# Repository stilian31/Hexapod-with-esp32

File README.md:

# Hexapod-with-esp32
this is a custom control board for a six-legged (hexapod) robot. It’s built around the ESP32-S3 WROOM and uses two PCA9685 drivers to precisely control all servos. The robot can be easily controlled via a joystick, making movement intuitive and fun. Designed for DIY robotics projects and expandable with sensors or LEDs.
The 3D model of the hexapod IS NOT mine.I've adapted the 3D model for my PCB :)
If you have any questions you can text me on instagram @funtronics_ or @stilianskordas and on my gmail - stilianskordas08@gmail.com :). I will answer any time.

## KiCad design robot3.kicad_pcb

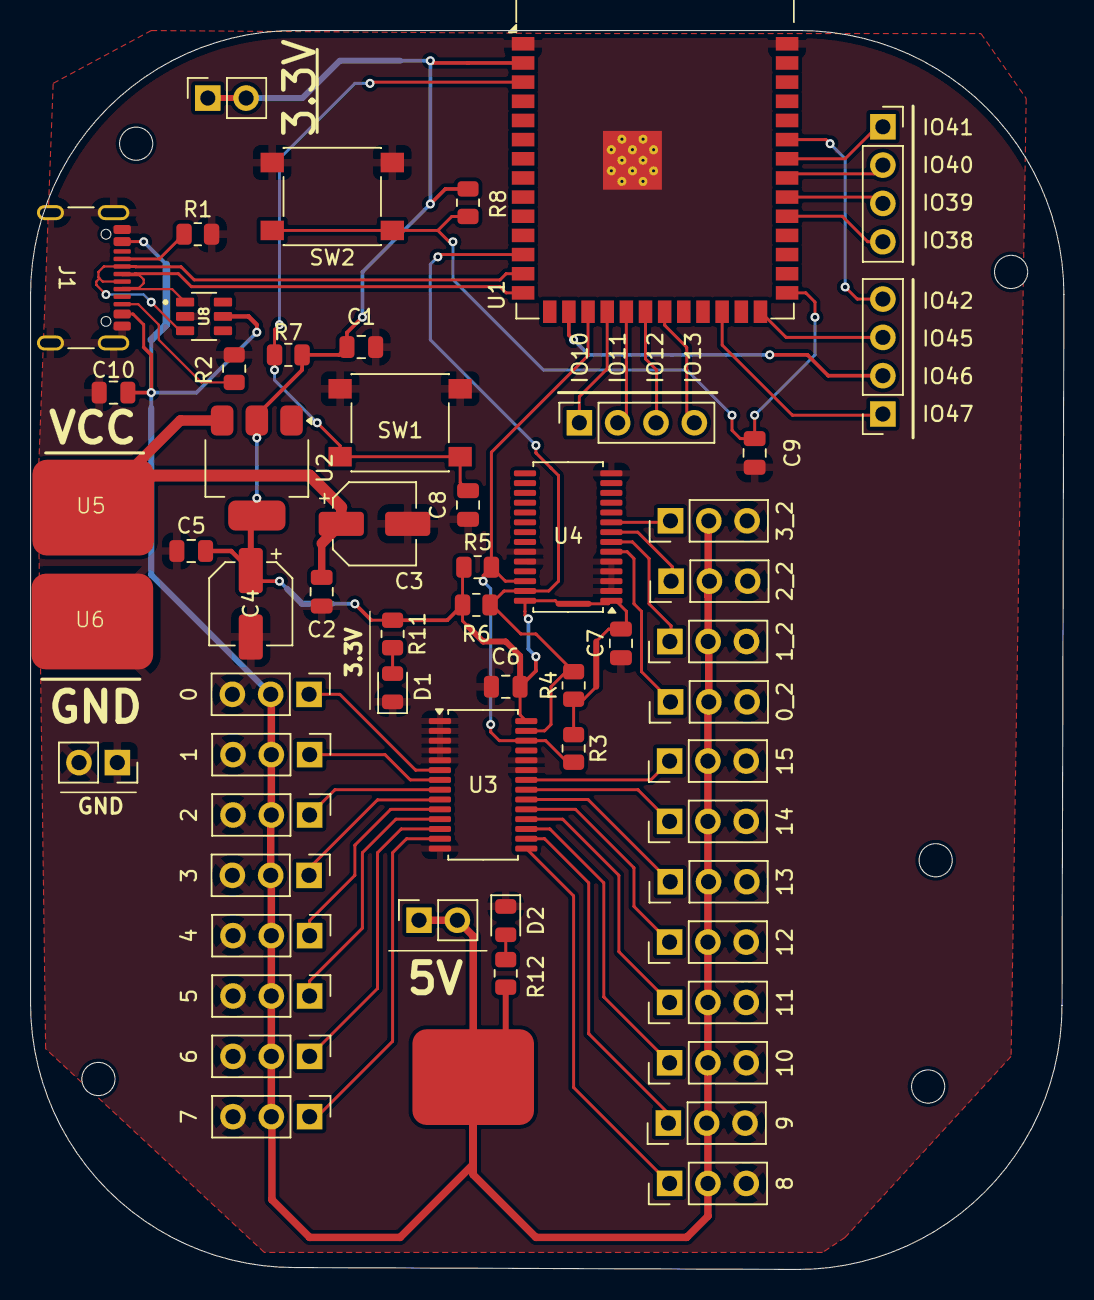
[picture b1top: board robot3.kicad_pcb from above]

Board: 2 copper layers, 68.5 x 82.1 mm, 59 parts (0 on the bottom side), 46 nets.

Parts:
0, 0_2, 1, 2, 2_2, 3, 4, 5, 6, 7, 8, 9, 10, 11, 12, 13, 14, 15: Conn_01x03_Pin; PinHeader_1x03_P2.54mm_Vertical
C1, C2, C5, C6, C7, C8, C9, C10: 100nF; C_0805_2012Metric
C3, C4: 10uF; CP_Elec_5x5.4
D1, D2: LED; LED_0805_2012Metric
J1: USB_C_Receptacle_USB2.0_16P; USB_C_Receptacle_GCT_USB4105-xx-A_16P_TopMnt_Horizontal
J19, J21: Conn_01x03_Pin; PinHeader_1x03_P2.54mm_Vertical
J22, J23, J24: Conn_01x04_Pin; PinSocket_1x04_P2.54mm_Vertical
J26, J27, J28: Conn_01x02_Pin; PinSocket_1x02_P2.54mm_Vertical
R1, R2: 5.1k; R_0805_2012Metric
R3, R5, R11, R12: R; R_0805_2012Metric
R4, R6: 4.7k; R_0805_2012Metric
R7, R8: 10k; R_0805_2012Metric
SW1, SW2: SW_Push; SW_SPST_PTS645
U1: ESP32-S3-WROOM-1
U2: AMS1117-3.3; SOT-223-3_TabPin2
U3, U4: PCA9685PW; TSSOP-28_4.4x9.7mm_P0.65mm
U5, U6, U7: pad
U8: USBLC6-2SC6

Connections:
+3.3V: C1.2, C4.1, C5.2, C6.2, C7.2, J27.1, J27.2, R3.1, R4.1, R5.1, R6.1, R7.1, R8.1, R11.1, U1.2 (3V3), U2.2 (VO), U3.28 (VDD), U4.1 (A0), U4.28 (VDD)
+5V: 0.2, 0_2.2, 1.2, 2.2, 2_2.2, 3.2, 4.2, 5.2, 6.2, 7.2, 8.2, 9.2, 10.2, 11.2, 12.2, 13.2, 14.2, 15.2, C10.1, J1.A4 (VBUS), J1.A9 (VBUS), J1.B4 (VBUS), J1.B9 (VBUS), J19.2, J21.2, J28.1, J28.2, R12.1, U7.1, U8.5
D+: J1.A6 (D+), J1.B6 (D+), U1.14 (USB_D+), U8.1
D-: J1.A7 (D-), J1.B7 (D-), U1.13 (USB_D-), U8.3
GND: 0.3, 0_2.3, 1.3, 2.3, 2_2.3, 3.3, 4.3, 5.3, 6.3, 7.3, 8.3, 9.3, 10.3, 11.3, 12.3, 13.3, 14.3, 15.3, C1.1, C2.1, C3.2, C4.2, C5.1, C6.1, C7.1, C8.2, C9.2, C10.2, D1.1 (K), D2.1 (K), J1.A1 (GND), J1.A12 (GND), J1.B1 (GND), J1.B12 (GND), J1.S1 (SHIELD), J19.3, J21.3, J26.1, J26.2, R1.2, R2.2, SW1.2, SW2.2, U1.1 (GND), U1.40 (GND), U1.41 (GND), U3.1 (A0), U3.2 (A1), U3.3 (A2), U3.4 (A3), U3.5 (A4), U3.14 (VSS), U3.23 (~OE), U3.24 (A5), U4.2 (A1), U4.3 (A2), U4.4 (A3), U4.5 (A4), U4.14 (VSS), U4.23 (~OE), U4.24 (A5), U6.1, U8.2
IO0: C9.1, R8.2, SW2.1, U1.27 (IO0)
IO8 SDA: R4.2, R6.2, U1.12 (IO8), U3.27 (SDA), U4.27 (SDA)
IO9 SCL: R3.2, R5.2, U1.17 (IO9), U3.26 (SCL), U4.26 (SCL)
LED0: 0.1, U3.6 (LED0)
LED0_2: 0_2.1, U4.6 (LED0)
LED1: 1.1, U3.7 (LED1)
LED1_2: J19.1, U4.7 (LED1)
LED2: 2.1, U3.8 (LED2)
LED2_2: 2_2.1, U4.8 (LED2)
LED3: 3.1, U3.9 (LED3)
LED3_2: J21.1, U4.9 (LED3)
LED4: 4.1, U3.10 (LED4)
LED5: 5.1, U3.11 (LED5)
LED6: 6.1, U3.12 (LED6)
LED7: 7.1, U3.13 (LED7)
LED8: 8.1, U3.15 (LED8)
LED9: 9.1, U3.16 (LED9)
LED10: 10.1, U3.17 (LED10)
LED11: 11.1, U3.18 (LED11)
LED12: 12.1, U3.19 (LED12)
LED13: 13.1, U3.20 (LED13)
LED14: 14.1, U3.21 (LED14)
LED15: 15.1, U3.22 (LED15)
unnamed: D1.2 (A), R11.2
unnamed: D2.2 (A), R12.2
unnamed: J1.A5 (CC1), R1.1
unnamed: J1.B5 (CC2), R2.1
unnamed: J22.1, U1.34 (IO41)
unnamed: J22.2, U1.33 (IO40)
unnamed: J22.3, U1.32 (IO39)
unnamed: J22.4, U1.31 (IO38)
unnamed: J23.1, U1.24 (IO47)
unnamed: J23.2, U1.16 (IO46)
unnamed: J23.3, U1.26 (IO45)
unnamed: J23.4, U1.35 (IO42)
unnamed: J24.1, U1.18 (IO10)
unnamed: J24.2, U1.19 (IO11)
unnamed: J24.3, U1.20 (IO12)
unnamed: J24.4, U1.21 (IO13)
unnamed: C8.1, R7.2, SW1.1, U1.3 (EN)
VCC: C2.2, C3.1, U2.3 (VI), U5.1

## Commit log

2026-01-02 Update README with note on 3D model adaptation
    Added a note about the 3D model adaptation for the PCB.
2026-01-02 Fix typo in README description
    Corrected a typo in the project description.
2026-01-02 Include contact details in README
    Added contact information for inquiries.
